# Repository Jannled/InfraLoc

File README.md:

# InfraLoc
Infrared angle estimation for mobile robots

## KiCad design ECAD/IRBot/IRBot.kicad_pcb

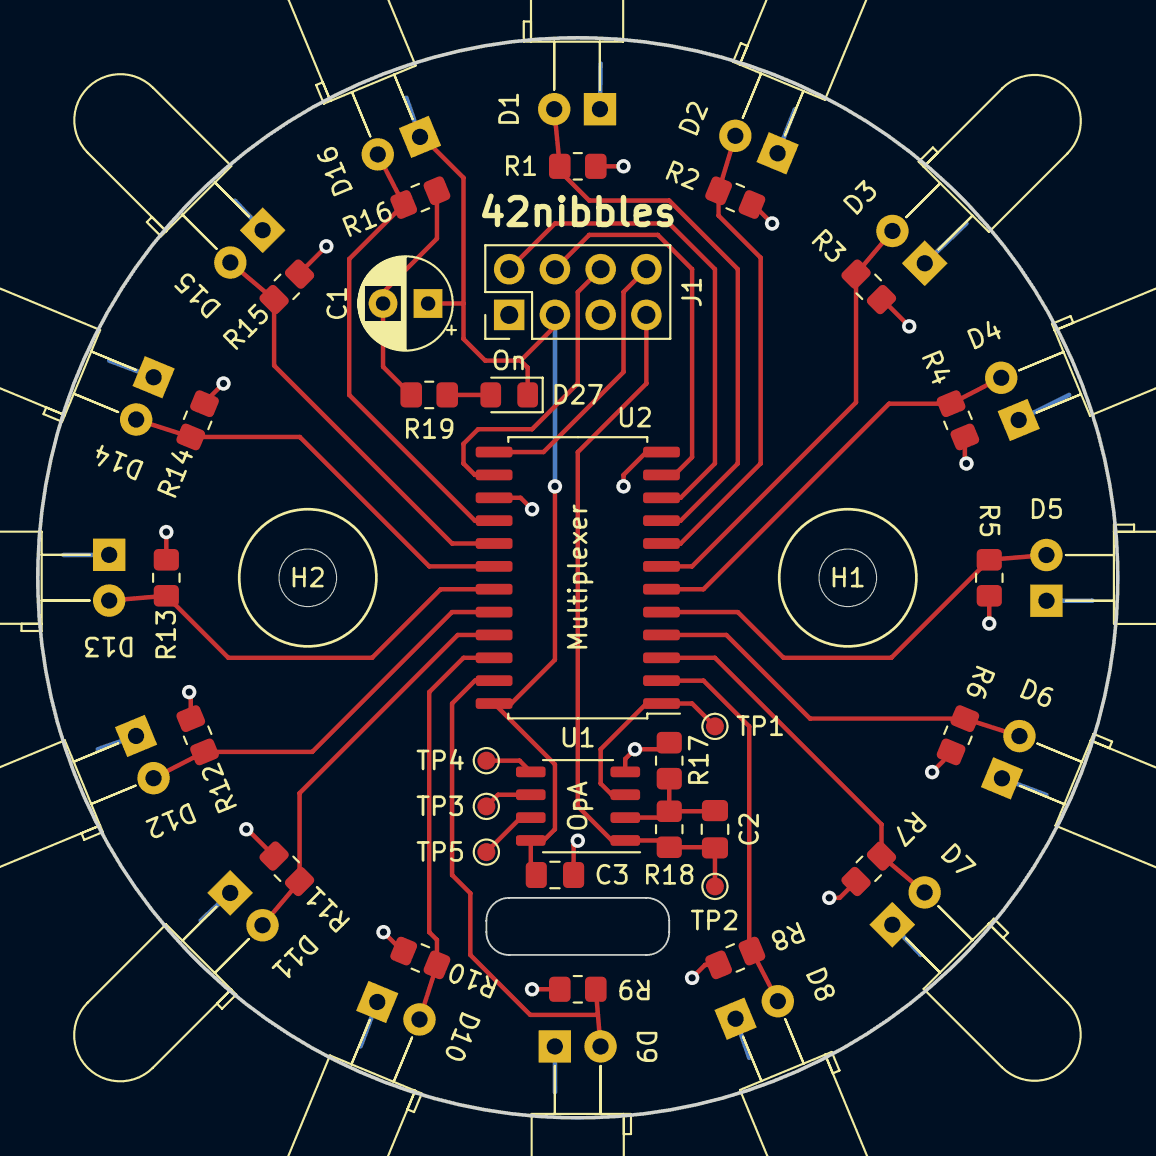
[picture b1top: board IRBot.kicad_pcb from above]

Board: 2 copper layers, 60.0 x 60.0 mm, 49 parts (0 on the bottom side), 29 nets.

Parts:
C1: 10uF; CP_Radial_D5.0mm_P2.50mm
C2: 10pF; C_0805_2012Metric_Pad1.18x1.45mm_HandSolder
C3: 100nF; C_0805_2012Metric_Pad1.18x1.45mm_HandSolder
D1, D2, D3, D4, D5, D6, D7, D8, D9, D10, D11, D12, D13, D14, D15, D16: D_Photo; LED_D5.0mm_Horizontal_O3.81mm_Z3.0mm
D27: LED; LED_0805_2012Metric_Pad1.15x1.40mm_HandSolder
H1, H2: MountingHole; MountingHole_3.2mm_M3_DIN965
J1: Conn_02x04_Odd_Even; PinHeader_2x04_P2.54mm_Vertical
R1, R2, R3, R4, R5, R6, R7, R8, R9, R10, R11, R12, R13, R14, R15, R16, R18: R; R_0805_2012Metric_Pad1.20x1.40mm_HandSolder
R17: 150k; R_0805_2012Metric_Pad1.20x1.40mm_HandSolder
R19: 250R; R_0805_2012Metric_Pad1.20x1.40mm_HandSolder
TP1: IR_Signal; TestPoint_Pad_D1.0mm
TP2: Preamp; TestPoint_Pad_D1.0mm
TP3: 2-; TestPoint_Pad_D1.0mm
TP4: 2+; TestPoint_Pad_D1.0mm
TP5: 2Out; TestPoint_Pad_D1.0mm
U1: LM358; SOP-8_3.9x4.9mm_P1.27mm
U2: 74HC4067D; SOIC-24W_7.5x15.4mm_P1.27mm

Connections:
/IR Empfänger/Out: C2.2, J1.7, R18.2, TP2.1, U1.1
/IR Empfänger/S0: J1.2, U2.10 (S0)
/IR Empfänger/S1: J1.4, U2.11 (S1)
/IR Empfänger/S2: J1.6, U2.14 (S2)
/IR Empfänger/S3: J1.8, U2.13 (S3)
GND: C1.2, C3.2, J1.1, R1.2, R2.2, R3.2, R4.2, R5.2, R6.2, R7.2, R8.2, R9.2, R10.2, R11.2, R12.2, R13.2, R14.2, R15.2, R16.2, R17.1, R19.2, U1.4 (V-), U2.12 (GND), U2.15 (~E)
IRsig: TP1.1, U1.3 (+), U2.1 (COM)
unnamed: D1.2 (A), R1.1, U2.9 (I0)
unnamed: D2.2 (A), R2.1, U2.8 (I1)
unnamed: D3.2 (A), R3.1, U2.7 (I2)
unnamed: D4.2 (A), R4.1, U2.6 (I3)
unnamed: D5.2 (A), R5.1, U2.5 (I4)
unnamed: D6.2 (A), R6.1, U2.4 (I5)
unnamed: D7.2 (A), R7.1, U2.3 (I6)
unnamed: D8.2 (A), R8.1, U2.2 (I7)
unnamed: D9.2 (A), R9.1, U2.23 (I8)
unnamed: D10.2 (A), R10.1, U2.22 (I9)
unnamed: D11.2 (A), R11.1, U2.21 (I10)
unnamed: D12.2 (A), R12.1, U2.20 (I11)
unnamed: D13.2 (A), R13.1, U2.19 (I12)
unnamed: D14.2 (A), R14.1, U2.18 (I13)
unnamed: D15.2 (A), R15.1, U2.17 (I14)
unnamed: D16.2 (A), R16.1, U2.16 (I15)
unnamed: D27.2 (A), R19.1
unnamed: TP5.1, U1.7
unnamed: C2.1, R17.2, R18.1, U1.2 (-)
unnamed: TP4.1, U1.5 (+)
unnamed: TP3.1, U1.6 (-)
VCC: C1.1, C3.1, D1.1 (K), D2.1 (K), D3.1 (K), D4.1 (K), D5.1 (K), D6.1 (K), D7.1 (K), D8.1 (K), D9.1 (K), D10.1 (K), D11.1 (K), D12.1 (K), D13.1 (K), D14.1 (K), D15.1 (K), D16.1 (K), D27.1 (K), J1.3, U1.8 (V+), U2.24 (VCC)

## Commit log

2023-03-01 Push base
2023-05-26 Better Serial Plotter
2023-05-29 Scope add multi channel option
2023-05-29 Cleanup Code for Fast Reader Scope
2023-05-29 Fix type check errors
2023-08-31 Wanted to update but then decided to use Matlab
2023-09-26 Restructure Repo to push hardware
2023-09-26 Fix broken schematic
2023-10-11 Update Matlab Code for new Graphics
